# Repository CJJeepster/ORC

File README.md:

# ORC
WSU Capstone 2025

ORC is a active suspension system for an RC car, in this case RC4WD's Trail finder 2. The design documentation, source code, python code, custom parts, schematics, and PCBs are included in their own folders. 

The source code is intended to be built with Espressif's ESP-ID v5.4.0, which can be a standalone toolchain, or VScode extension. 
The python code is run with python 3.12 using the following libraries: csv, matplotlib, numpy, scipy, and collections. This will take the logged data, calculate some statistics, and plot the repeated runs.
The custom parts were designed in FreeCAD 1.0.0, with both STL files and the original files included. 
The schematics and PCBs were designed in KiCAD 8.0. A seperate "revisions" document details the shortcomings of this design. Fixes are not yet implemented to preserve the current state of the board and save development time.

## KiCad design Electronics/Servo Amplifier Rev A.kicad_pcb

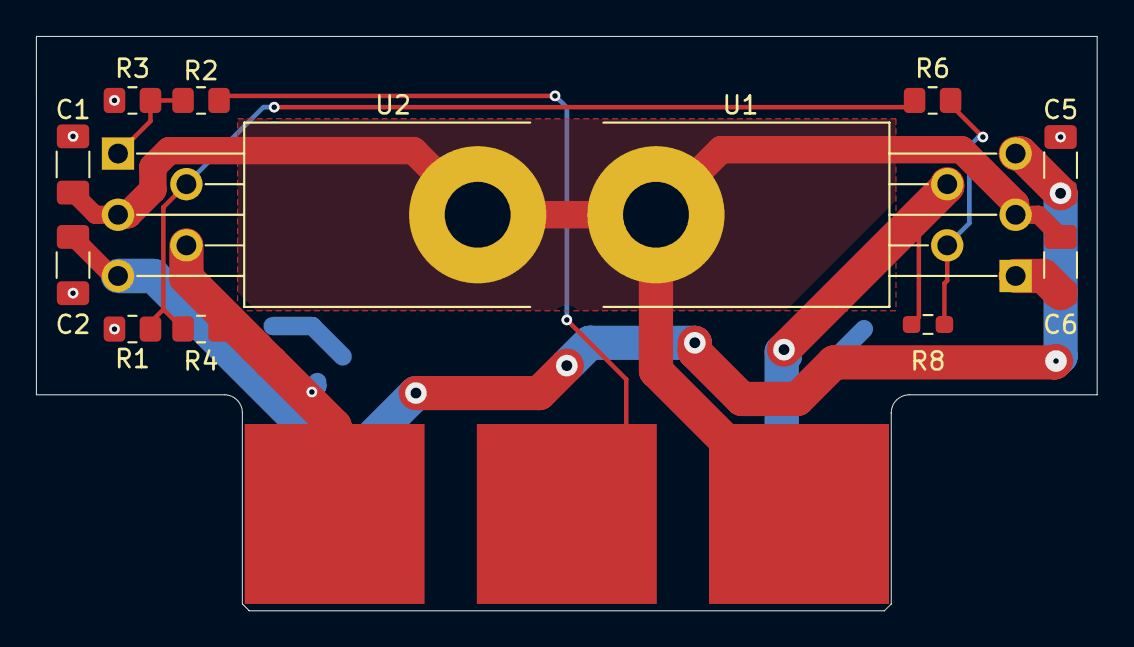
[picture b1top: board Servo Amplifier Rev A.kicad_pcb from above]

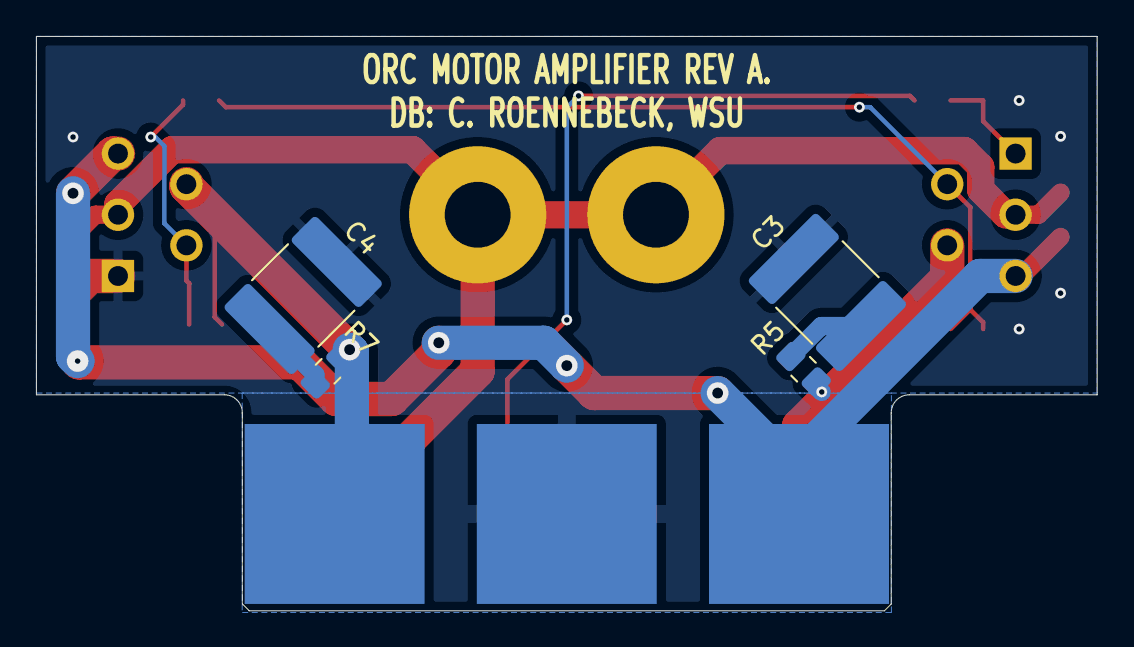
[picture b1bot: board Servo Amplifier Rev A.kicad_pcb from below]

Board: 2 copper layers, 58.9 x 31.9 mm, 17 parts (4 on the bottom side), 11 nets.

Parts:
C1, C2, C5, C6: .1µ; C_1206_3216Metric_Pad1.33x1.80mm_HandSolder
C3, C4: .22µ; C_2220_5750Metric_Pad1.97x5.40mm_HandSolder
J1: Conn_01x06; MOLEX-45719-0005_PCB_EDGE
R1: 10k; R_0805_2012Metric_Pad1.20x1.40mm_HandSolder
R2: 213 ±0.5%; R_0805_2012Metric_Pad1.20x1.40mm_HandSolder
R3: 100 ±0.5%; R_0805_2012Metric_Pad1.20x1.40mm_HandSolder
R4: 100k; R_0805_2012Metric_Pad1.20x1.40mm_HandSolder
R5, R7: 6.98k; R_0805_2012Metric_Pad1.20x1.40mm_HandSolder
R6: 99k; R_0805_2012Metric_Pad1.20x1.40mm_HandSolder
R8: 990k; R_0603_1608Metric_Pad0.98x0.95mm_HandSolder
U1, U2: LM675; TO-220-5_P3.4x3.8mm_StaggerOdd_Lead7.13mm_TabDown_504222B_HS

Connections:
/Input: J1.A8 (Pin_3), R2.2
/Out A: J1.A13 (Pin_5), R4.2, R5.1, U1.4
/OutB: J1.B3 (Pin_2), R7.1, R8.2, U2.4
GND: C1.2, C2.2, C3.2, C4.2, C5.2, C6.2, J1.B8 (Pin_4), R1.2, R3.2, U2.1 (+)
unnamed: C3.1, R5.2
unnamed: C4.1, R7.2
unnamed: R2.1, R3.1, U1.1 (+)
unnamed: R1.1, R4.1, R6.2, U1.2 (-)
unnamed: R6.1, R8.1, U2.2 (-)
VCC: C2.1, C5.1, J1.B13 (Pin_6), U1.5 (V+), U2.5 (V+)
VEE: C1.1, C6.1, J1.A3 (Pin_1), U1.3 (V-), U2.3 (V-)

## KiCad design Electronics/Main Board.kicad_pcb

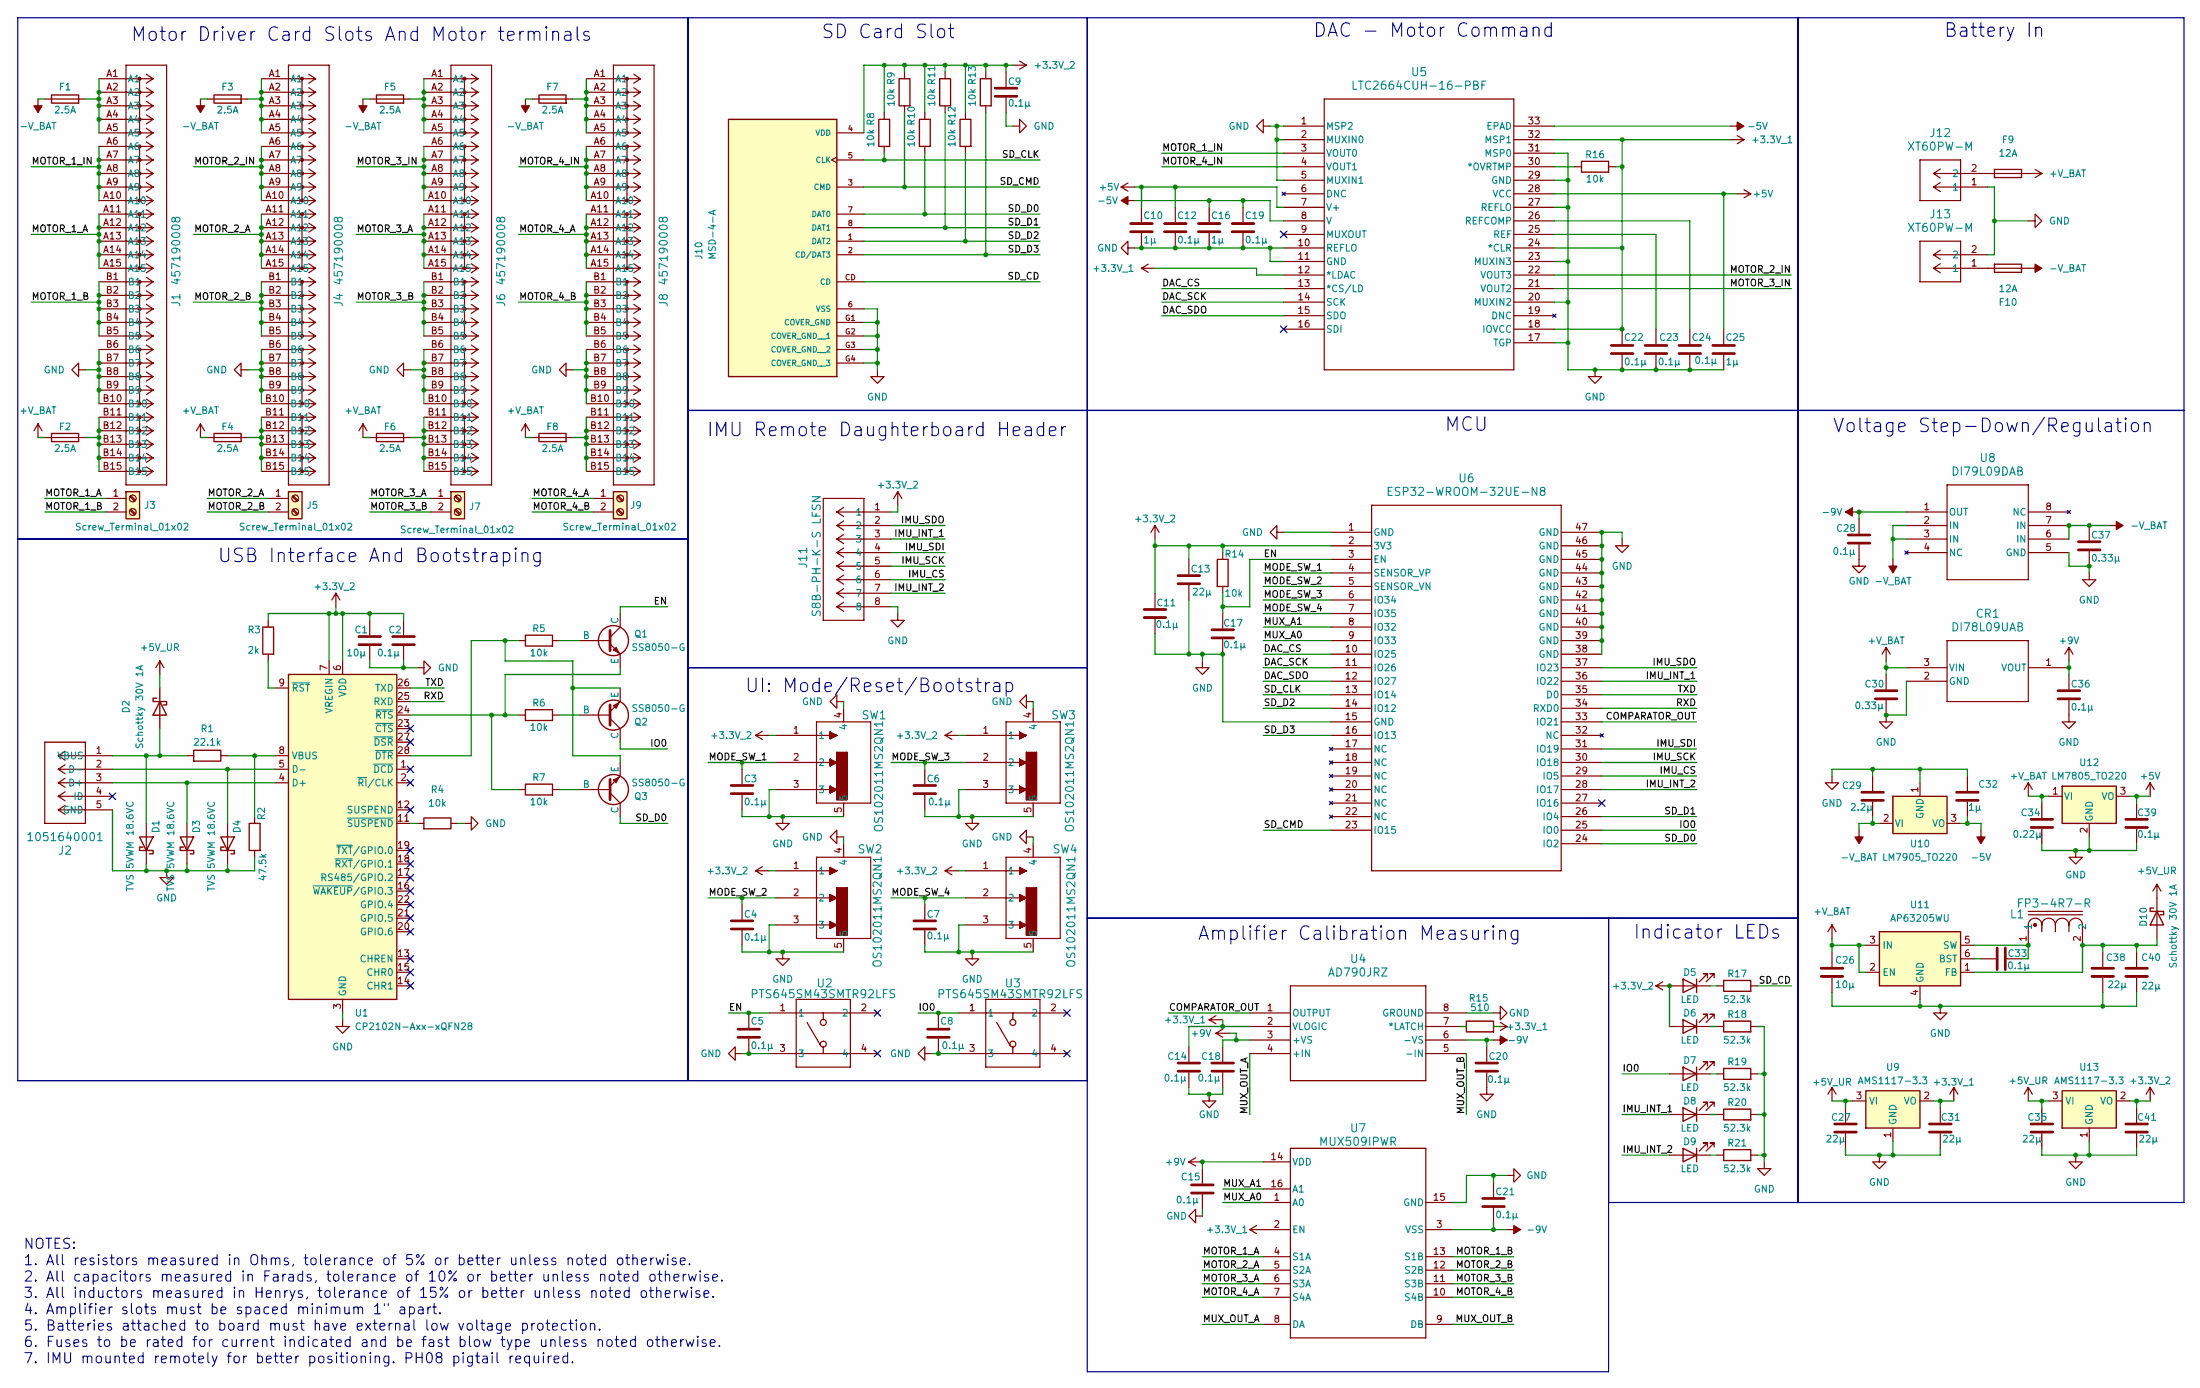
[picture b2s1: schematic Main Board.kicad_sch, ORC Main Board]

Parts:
C1, C26: 10μ; C_1206_3216Metric_Pad1.33x1.80mm_HandSolder
C2, C3, C4, C5, C6, C7, C8, C9, C11, C12, C14, C15, C17, C18, C19, C20, C21, C22, C23, C24, C28, C33, C36, C39: 0.1μ; C_1206_3216Metric_Pad1.33x1.80mm_HandSolder
C10, C16, C25, C32: 1μ; C_1206_3216Metric_Pad1.33x1.80mm_HandSolder
C13, C27, C31, C35, C38, C40, C41: 22μ; C_1206_3216Metric_Pad1.33x1.80mm_HandSolder
C29: 2.2μ; C_1206_3216Metric_Pad1.33x1.80mm_HandSolder
C30, C37: 0.33μ; C_1206_3216Metric_Pad1.33x1.80mm_HandSolder
C34: 0.22μ; C_1206_3216Metric_Pad1.33x1.80mm_HandSolder
CR1: DI78L09UAB; SOT-89_STM
D1, D3, D4: TVS 5VWM 18.6VC; D_0402_1005Metric_Pad0.77x0.64mm_HandSolder
D2, D10: Schottky 30V 1A; D_SOD-323_HandSoldering
D5, D6, D7, D8, D9: LED; LED_PLCC-2_3.4x3.0mm_KA
F1, F2, F3, F4, F5, F6, F7, F8: 2.5A; Fuse_1206_3216Metric_Pad1.42x1.75mm_HandSolder
F9, F10: 12A; Fuse_1206_3216Metric_Pad1.42x1.75mm_HandSolder
J1, J4, J6, J8: 457190008; CONN_SD-45719-001_3SEG_MOL
J2: 1051640001; CON00906_5_MOL
J3, J5, J7, J9: Screw_Terminal_01x02; TerminalBlock_TE_282834-2_1x02_P2.54mm_Horizontal
J10: MSD-4-A; CUI_MSD-4-A; PARTREV 1.0
J11: S8B-PH-K-S LFSN; CONN8_S8B-PH-K-S_JST
J12, J13: XT60PW-M; CONN_XT60PW-M_AMA
L1: FP3-4R7-R; FP3
Q1, Q2, Q3: SS8050-G; SOT-23-3
R1: 22.1k; R_1206_3216Metric_Pad1.30x1.75mm_HandSolder
R2: 47.5k; R_1206_3216Metric_Pad1.30x1.75mm_HandSolder
R3: 2k; R_1206_3216Metric_Pad1.30x1.75mm_HandSolder
R4, R5, R6, R7, R8, R9, R10, R11, R12, R13, R14, R16: 10k; R_1206_3216Metric_Pad1.30x1.75mm_HandSolder
R15: 510; R_1206_3216Metric_Pad1.30x1.75mm_HandSolder
R17, R18, R19, R20, R21: 52.3k; R_1206_3216Metric_Pad1.30x1.75mm_HandSolder
SW1, SW2, SW3, SW4: OS102011MS2QN1; SPDT_OS102011_CNK
U1: CP2102N-Axx-xQFN28; QFN-28-1EP_5x5mm_P0.5mm_EP3.35x3.35mm
U2, U3: PTS645SM43SMTR92LFS; SWITCH_43SMTR92LFS
U4: AD790JRZ; R_8_ADI
U5: LTC2664CUH-16-PBF; UH_32_ADI
U6: ESP32-WROOM-32UE-N8; ESP32-WROOM-32UE_EXP
U7: MUX509IPWR; PW0016A_N
U8: DI79L09DAB; SO8NB_STH
U9, U13: AMS1117-3.3; SOT-223-3_TabPin2
U10: LM7905_TO220; TO-220-3_Vertical
U11: AP63205WU; TSOT-23-6
U12: LM7805_TO220; TO-220-3_Vertical

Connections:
+3.3V_1: C14.1, C22.1, C31.1, R15.2, R16.2, U4.2 (VLOGIC), U5.12 (*LDAC), U5.18 (IOVCC), U5.24 (*CLR), U5.32 (MSP1), U7.2 (EN), U9.2 (VO)
+3.3V_2: C1.2, C2.1, C9.1, C11.1, C13.1, C41.1, D5.2 (A), D6.2 (A), J10.4 (VDD), J11.1, R3.1, R8.1, R9.1, R10.1, R11.1, R12.1, R13.1, R14.1, SW1.1, SW2.1, SW3.1, SW4.1, U1.6 (VDD), U1.7 (VREGIN), U6.2 (3V3), U13.2 (VO)
+5V: C10.1, C12.1, C25.1, C39.1, U5.7 (V+), U5.28 (VCC), U12.3 (VO)
+5V_UR: C27.1, C35.1, D2.1 (K), D10.1 (K), U9.3 (VI), U13.3 (VI)
+9V: C15.2, C18.1, C36.1, CR1.1 (VOUT), U4.3 (+VS), U7.14 (VDD)
+V_BAT: C26.1, C30.1, C34.1, CR1.3 (VIN), F2.1, F4.1, F6.1, F8.1, F9.1, U11.2 (EN), U11.3 (IN), U12.1 (VI)
-5V: C16.1, C19.1, C32.2, U5.8 (V), U5.33 (EPAD), U10.3 (VO)
-9V: C20.1, C21.2, C28.1, U4.6 (-VS), U7.3 (VSS), U8.1 (OUT)
-V_BAT: C29.2, C37.1, F1.1, F3.1, F5.1, F7.1, F10.1, U8.2 (IN), U8.3 (IN), U8.6 (IN), U8.7 (IN), U10.2 (VI)
/COMPARATOR_OUT: U4.1 (OUTPUT), U6.33 (IO21)
/DAC_CS: U5.13 (*CS/LD), U6.10 (IO25)
/DAC_SCK: U5.14 (SCK), U6.11 (IO26)
/DAC_SDO: U5.15 (SDO), U6.12 (IO27)
/EN: C5.1, C17.1, Q1.1 (C), R14.2, U2.1, U6.3 (EN)
/IMU_CS: J11.6, U6.29 (IO5)
/IMU_INT_1: D8.2 (A), J11.3, U6.36 (IO22)
/IMU_INT_2: D9.2 (A), J11.7, U6.28 (IO17)
/IMU_SCK: J11.5, U6.30 (IO18)
/IMU_SDI: J11.4, U6.31 (IO19)
/IMU_SDO: J11.2, U6.37 (IO23)
/IO0: C8.1, D7.2 (A), Q2.1 (C), U3.1, U6.25 (IO0)
/MODE_SW_1: C3.2, SW1.2, U6.4 (SENSOR_VP)
/MODE_SW_2: C4.2, SW2.2, U6.5 (SENSOR_VN)
/MODE_SW_3: C6.2, SW3.2, U6.6 (IO34)
/MODE_SW_4: C7.2, SW4.2, U6.7 (IO35)
/MOTOR_1_A: J1.A11, J1.A12, J1.A13, J1.A14, J1.A15, J3.1, U7.4 (S1A)
/MOTOR_1_B: J1.B1, J1.B2, J1.B3, J1.B4, J1.B5, J3.2, U7.13 (S1B)
/MOTOR_1_IN: J1.A6, J1.A7, J1.A8, J1.A9, J1.A10, U5.3 (VOUT0)
/MOTOR_2_A: J4.A11, J4.A12, J4.A13, J4.A14, J4.A15, J5.1, U7.5 (S2A)
/MOTOR_2_B: J4.B1, J4.B2, J4.B3, J4.B4, J4.B5, J5.2, U7.12 (S2B)
/MOTOR_2_IN: J4.A6, J4.A7, J4.A8, J4.A9, J4.A10, U5.22 (VOUT3)
/MOTOR_3_A: J6.A11, J6.A12, J6.A13, J6.A14, J6.A15, J7.1, U7.6 (S3A)
/MOTOR_3_B: J6.B1, J6.B2, J6.B3, J6.B4, J6.B5, J7.2, U7.11 (S3B)
/MOTOR_3_IN: J6.A6, J6.A7, J6.A8, J6.A9, J6.A10, U5.21 (VOUT2)
/MOTOR_4_A: J8.A11, J8.A12, J8.A13, J8.A14, J8.A15, J9.1, U7.7 (S4A)
/MOTOR_4_B: J8.B1, J8.B2, J8.B3, J8.B4, J8.B5, J9.2, U7.10 (S4B)
/MOTOR_4_IN: J8.A6, J8.A7, J8.A8, J8.A9, J8.A10, U5.4 (VOUT1)
/MUX_A0: U6.9 (IO33), U7.1 (A0)
/MUX_A1: U6.8 (IO32), U7.16 (A1)
/MUX_OUT_A: U4.4 (+IN), U7.8 (DA)
/MUX_OUT_B: U4.5 (-IN), U7.9 (DB)
/RXD: U1.25 (RXD), U6.34 (RXD0)
/SD_CD: J10.CD, R17.2
/SD_CLK: J10.5 (CLK), R8.2, U6.13 (IO14)
/SD_CMD: J10.3 (CMD), R9.2, U6.23 (IO15)
/SD_D0: J10.7 (DAT0), Q3.1 (C), R10.2, U6.24 (IO2)
/SD_D1: J10.8 (DAT1), R11.2, U6.26 (IO4)
/SD_D2: J10.1 (DAT2), R12.2, U6.14 (IO12)
/SD_D3: J10.2 (CD/DAT3), R13.2, U6.16 (IO13)
/TXD: U1.26 (TXD), U6.35 (D0)
GND: C1.1, C2.2, C3.1, C4.1, C5.2, C6.1, C7.1, C8.2, C9.2, C10.2, C11.2, C12.2, C13.2, C14.2, C15.1, C16.2, C17.2, C18.2, C19.2, C20.2, C21.1, C22.2, C23.2, C24.2, C25.2, C26.2, C27.2, C28.2, C29.1, C30.2, C31.2, C32.1, C34.2, C35.2, C36.2, C37.2, C38.2, C39.2, C40.2, C41.2, CR1.2 (GND), D1.1 (K), D3.1 (K), D4.1 (K), J1.B6, J1.B7, J1.B8, J1.B9, J1.B10, J2.5 (GND), J2.6, J2.7, J2.8, J2.9, J2.10, J2.11, J4.B6, J4.B7, J4.B8, J4.B9, J4.B10, J6.B6, J6.B7, J6.B8, J6.B9, J6.B10, J8.B6, J8.B7, J8.B8, J8.B9, J8.B10, J10.6 (VSS), J10.G1 (COVER_GND), J10.G2 (COVER_GND__1), J10.G3 (COVER_GND__2), J10.G4 (COVER_GND__3), J11.8, J12.1, J13.2, R2.2, R4.1, R18.2, R19.2, R20.2, R21.2, SW1.3, SW1.4, SW1.5, SW2.3, SW2.4, SW2.5, SW3.3, SW3.4, SW3.5, SW4.3, SW4.4, SW4.5, U1.3 (GND), U1.29 (GND), U2.3, U3.3, U4.8 (GROUND), U5.1 (MSP2), U5.2 (MUXIN0), U5.5 (MUXIN1), U5.10 (REFLO), U5.11 (GND), U5.17 (TGP), U5.20 (MUXIN2), U5.23 (MUXIN3), U5.27 (REFLO), U5.29 (GND), U5.31 (MSP0), U6.1 (GND), U6.15 (GND), U6.38 (GND), U6.39 (GND), U6.40 (GND), U6.41 (GND), U6.42 (GND), U6.43 (GND), U6.44 (GND), U6.45 (GND), U6.46 (GND), U6.47 (GND), U7.15 (GND), U8.5 (GND), U9.1 (GND), U10.1 (GND), U11.4 (GND), U12.2 (GND), U13.1 (GND)
unnamed: D1.2 (A), D2.2 (A), J2.1 (VBUS), R1.2
unnamed: D3.2 (A), J2.3 (D+), U1.4 (D+)
unnamed: D4.2 (A), J2.2 (D-), U1.5 (D-)
unnamed: D5.1 (K), R17.1
unnamed: D6.1 (K), R18.1
unnamed: D7.1 (K), R19.1
unnamed: D8.1 (K), R20.1
unnamed: D9.1 (K), R21.1
unnamed: C38.1, C40.1, D10.2 (A), L1.2, U11.1 (FB)
unnamed: F1.2, J1.A1, J1.A2, J1.A3, J1.A4, J1.A5
unnamed: F2.2, J1.B11, J1.B12, J1.B13, J1.B14, J1.B15
unnamed: F3.2, J4.A1, J4.A2, J4.A3, J4.A4, J4.A5
unnamed: F4.2, J4.B11, J4.B12, J4.B13, J4.B14, J4.B15
unnamed: F5.2, J6.A1, J6.A2, J6.A3, J6.A4, J6.A5
unnamed: F6.2, J6.B11, J6.B12, J6.B13, J6.B14, J6.B15
unnamed: F7.2, J8.A1, J8.A2, J8.A3, J8.A4, J8.A5
unnamed: F8.2, J8.B11, J8.B12, J8.B13, J8.B14, J8.B15
unnamed: F9.2, J12.2
unnamed: F10.2, J13.1
unnamed: Q1.2 (B), R5.2
unnamed: Q1.3 (E), R6.1, R7.1, U1.24 (~RTS)
unnamed: Q2.2 (B), R6.2
unnamed: Q2.3 (E), Q3.3 (E), R5.1, U1.28 (~DTR)
unnamed: Q3.2 (B), R7.2
unnamed: R1.1, R2.1, U1.8 (VBUS)
unnamed: R3.2, U1.9 (~RST)
unnamed: R4.2, U1.11 (~SUSPEND)
unnamed: R15.1, U4.7 (*LATCH)
unnamed: R16.1, U5.30 (*OVRTMP)
unnamed: C23.1, U5.25 (REF)
unnamed: C24.1, U5.26 (REFCOMP)
unnamed: C33.2, U11.6 (BST)
unnamed: C33.1, L1.1, U11.5 (SW)

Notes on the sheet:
NOTES: 1. All resistors measured in Ohms, tolerance of 5% or better unless noted otherwise. 2. All capacitors measured in Farads, tolerance of 10% or better unless noted otherwise. 3. All inductors measured in Henrys, tolerance of 15% or better unless noted otherwise. 4. Amplifier slots must be spa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
UI: Mode/Reset/Bootstrap
Motor Driver Card Slots And Motor terminals
Voltage Step-Down/Regulation
SD Card Slot
IMU Remote Daughterboard Header
USB Interface And Bootstraping
MCU
DAC - Motor Command
Battery In
Indicator LEDs
Amplifier Calibration Measuring

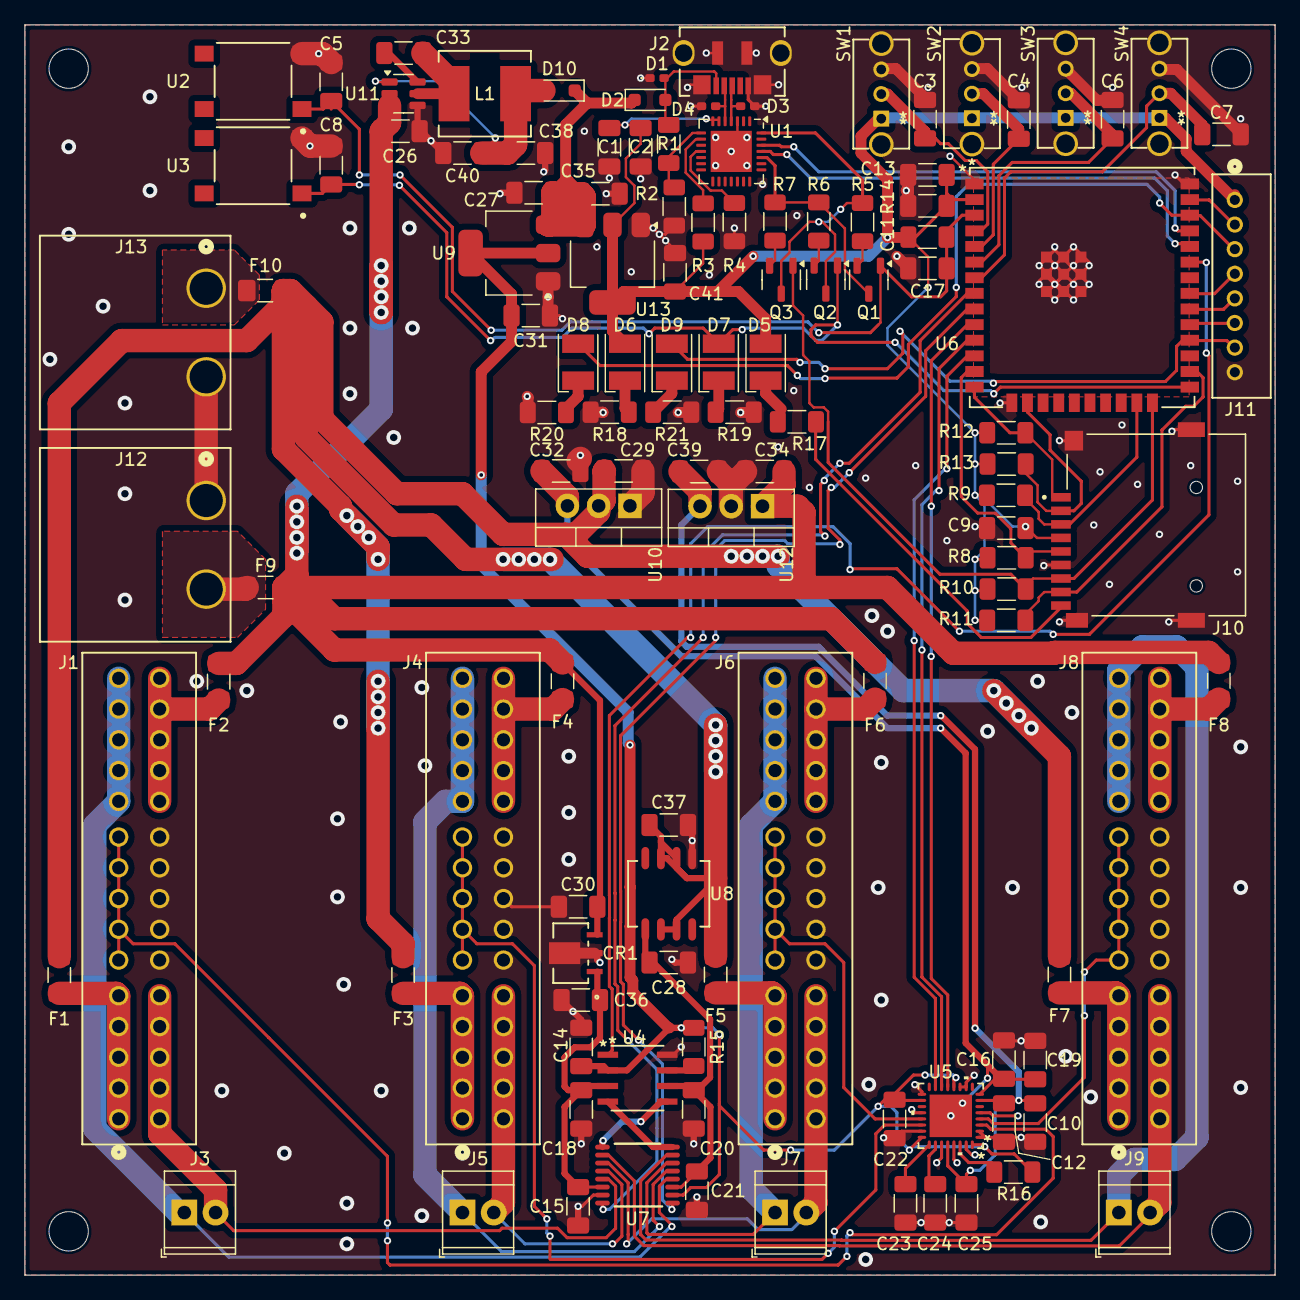
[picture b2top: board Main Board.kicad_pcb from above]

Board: 2 copper layers, 101.6 x 101.6 mm, 117 parts (0 on the bottom side), 84 nets.

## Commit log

2025-02-04 Push test
2025-02-05 DAC Library and Test Code Rev IR
2025-02-05 Fixed .gitignore -added build directory
2025-02-06 Add Transform Library
2025-02-11 Make IMU work from interupt (broken)
2025-02-12 Added PID library. IMU working, requires debug still
2025-02-14 IMU output chained to DAC, Need level based interrupts implemented.
2025-02-16 Add SD testing and functionality. Typo and Spacing fixes
2025-02-18 Added Calibration to the DACs. Will get within 3LSB of a true "zero" assuming minimal variance from theroretical zero. Adjustment direction may need modified.
2025-02-25 SD Page writing changes
2025-03-06 Bug fixes with DAC output, Renaming for clarification, Add startup pitch/roll/acceleration calibration, Add status LED output, Add Mode Switch configuration, better format for logging
2025-03-08 readability fixes, other consolidations
2025-03-11 Sampling rate issues fixed. Able to do 3khz. now tuning PIDs
2025-03-14 IMU filtering implemented. 3D models, schematics now tracked. Code commented in detail.
2025-03-21 PIDs tuned. Start switch wired to RC reciever. Battery inputs routed through relays. Camber test data collected and processed. DAC output code better clamped. Calibration bypassed, MUX is dead.
2025-03-21 Stability of Derivative (Jerk) fixed when starting and stopping log. Terrain and camber test data collected
2025-03-21 Vibration test added, both high and low speed
2025-03-22 Graphs changed to show only single run. Better for printing and easy understanding. T-test added. All current data re-ran
2025-03-27 Data collected and plots finalized. Compiled stats and poster included
2025-04-16 Documentation Updates
